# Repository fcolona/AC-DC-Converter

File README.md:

# Fonte de Tensão Variável

## Integrantes do Grupo
- Felipe Ferreira Colona - 15636525
- Arthur Martins Pereira - 16855601
- Gabriel Cordeiro Correa Silva - 16866642

## Descrição
O projeto se trata de uma fonte de tensão variável que, ao receber uma corrente alternada (AC), fornece uma corrente direta aproximadamente contínua (DC). Nesse contexto, deve ser possível regular a tensão de saída por meio de um potenciômetro, podendo escolher entre 3V e 12V e mantendo uma corrente de cerca de 100mA. Desse modo, a fonte deve ser capaz de carregar um celular sem causar danos.

## Componentes

| Quantidade      | Componente              | Valor    |
| --------------- | ----------------------- | -------  |
| 1x              | Ponte de diodos         | R$ 3,90  |
| 1x              | Capacitor               | R$ 4,40  |
| 1x              | Potenciômetro           | R$ 7,00  |
| 1x              | Diodo Zenner            | R$ 0,50  |
| 1x              | Transistor 2N2222       | R$ 2,55  |
| 5x              | Resistores 1/4W         | R$ 0,07  |
| 1x              | Resistor 2W             | R$ 1,20  |
| 1x              | LED                     | R$ 0,50  |
| 1x              | Jumper                  | R$ 0,70  |
| 1x              | Protoboard              | R$ 21,70 |
| TOTAL           |                         | R$ 42,80 |

#### Transformador
O transformador é responsável por diminuir o pico da tensão recebida da tomada de 180V para 18,1V. Essa transformação ocorre por meio da variação do campo magnético nas espiras do componente que causa uma indução de corrente elétrica.

#### Ponte de Diodo
A ponte de diodo é responsável por garantir que a corrente flua em somente um sentido ao longo do circuito. Isso é necessário, pois a tensão de entrada é uma senoide e, desse modo, possui uma parte negativa. Sendo assim, a ponte é composta por 4 diodos que, da forma em que estão dispostos, permitem a passagem de corrente em apenas um sentido.

#### Capacitor
O capacitor é responsável por continuar a fornecer tensão ao circuito mesmo nos mementos em que a senoide da tensão está com uma taxa de variação negativa, isto é, está diminuindo. Nesse sentido, o componente armazena carga quando a tensão está alta e libera carga quando a tensão de fora está menor do que a tensão do capacitor.

#### Resistor
O resistor é responsável por diminuir a corrente elétrica que chega a um outro componente. Isso é feito a fim de não ultrapassar a potência de operação do componente em questão e mantê-lo funcionando.

#### LED
O LED é responsável por facilitar a visualização do comportamento do circuito. Nesse sentido, o intuito é que ele se mantenha aceso durante todo o período. Assim, indicando que a corrente está de fato contínua (aproximadamente).

#### Diodo Zenner
O diodo zenner é reponsável por limitar a tensão máxima. No circuito em questão, ele limita a tensão em 13V que, após passar passar pelo transistor, se torna 12,3V.

#### Transistor
O transistor é responsável por amplificar o sinal que chega nele, de modo a fornecer 100 mA de corrente ao final do circuito.

#### Potenciômetro
O potenciômetro é responsável por possibilitar regular a tensão de saída (entre 3V e 12V).

## Circuito

[Link para o circuito](https://www.falstad.com/circuit/circuitjs.html?ctz=CQAgjCAMB0l3BWcMBMcUHYMGZIA4UA2ATmIxAUgpABZsKBTAWjDACgAnEQlG27FN1608VKmDhsA5iAFUefOdwSEoUThRp8EGVQi1C+VGhkkB3TdrCD9fGsVWQ2F+6teXaD9S68L+gvydsPgAvADcAewAbABcAQykGAB0ARzB6cWgMMDoEFDwwYnz8PDxsZnIqQXT1EM9VP3d3QXDo+MTU9OdDf3repy4mgT73cXhuhCK+yZsDJxdhukEhwXmKKdsKQipNpzAMbQMEaw8dVQgJeChoUkp4e-uIACUGAGcAS1f4gDsAYwYJgZGr5hGtCKUeptAt0-McAhC4eoYutliC7F5xCAWBhoPo8LoaAhcIRCMETjBCLpKXhiJB9qIDthyJcQAATBgAMziAFdYt0mF4lljCHZhmsWPleixtv02K8sdY8FLBWK1Fyoq8AQtlsMlEK1kK-EpoYNFiqAqDZOMwDxekL7V5BOyubyYkwogxWeA1GJYOwLMbhChhNCLMHRYI9WK2L9ZGheoG7Nd4CYQChsNBsDb0lpeKxCcFk3T1FxwUrEWWeuI0PybfJhEwRVW2GEFTKhdL60ZvTKwKIfdcEGwACrCiNxqu0a7pUqzudz4hYmCQGgoImQbaUyh9umLpgIG4YPAISjEfGbmjg5g5a6kYjdQVeM2Obp1lHgGUqMSv9vDN80OB1C9N8vzTYRmnAAA5ACVzYYDPxlR9VGqaC4BoOCwPRc5f0EFCYPQr0kI-YxhjwtCfx2KY31DYienDZsw3Ax0QxUbxMOUVRhkIVi1i41iuNBbpFl1VEXwsf9APomC2KkyTwOjCJ+G4bsANIWhMkcNMlOwNhFPjJtjEgNSAOuaotPjHTFIaFSjMXeNl2sJBcO4WQ2CAA)

## Design de PCB

## Imagem e Vídeo

## Cálculos

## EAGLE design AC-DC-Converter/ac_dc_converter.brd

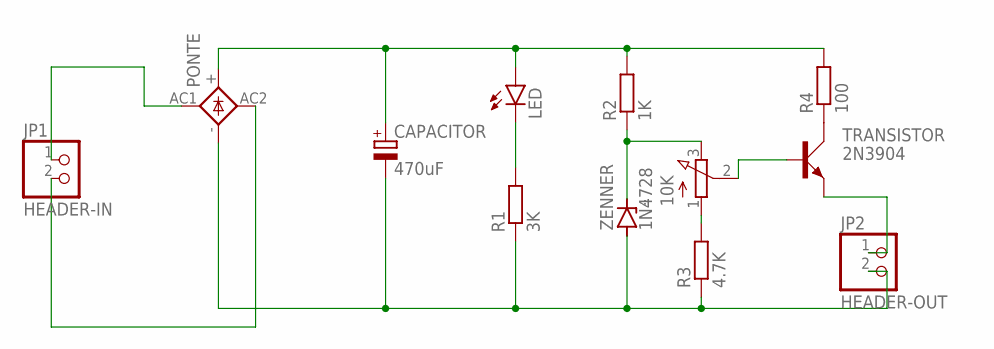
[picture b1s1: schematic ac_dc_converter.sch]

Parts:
CAPACITOR: 470uF; E5-10,5
JP1: HEADER-IN; 1X02
JP2: HEADER-OUT; 1X02
LED: LED5MM
PONTE: 1KAB
R1: 3K; 0204/7
R2: 1K; 0204/7
R3: 4.7K; 0204/7
R4: 100; 0204/7
TRANSISTOR: 2N3904; TO92D
ZENNER: 1N4728; DO41Z10
¨: 10K; 3RP/1610N

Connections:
unnamed: JP1.1, PONTE.AC1
unnamed: CAPACITOR.+, LED.A, PONTE.+, R2.2, R4.2
unnamed: R2.1, ZENNER.C, ¨.3 (E)
unnamed: CAPACITOR.-, JP2.2, PONTE.-, R1.1, R3.1, ZENNER.A
unnamed: JP1.2, PONTE.AC2
unnamed: LED.K (C), R1.2
unnamed: TRANSISTOR.B, ¨.2 (S)
unnamed: R4.1, TRANSISTOR.C
unnamed: JP2.1, TRANSISTOR.E
unnamed: R3.2, ¨.1 (A)

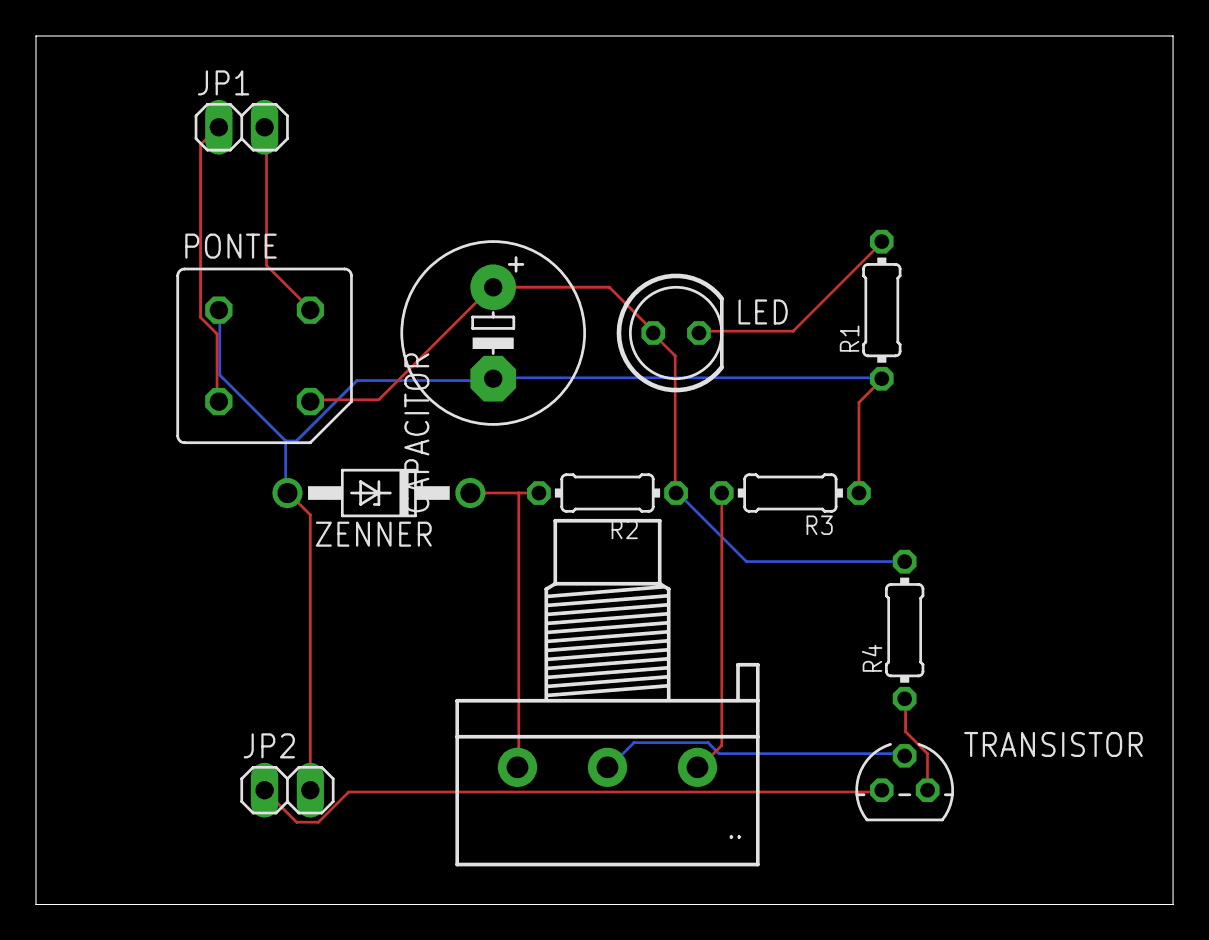
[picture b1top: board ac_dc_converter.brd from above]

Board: 2 copper layers, 63.2 x 48.2 mm, 12 parts (0 on the bottom side), 10 nets.

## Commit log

2025-06-02 add description and components explanations
2025-06-13 add circuit in Falstad and add calculations
2025-06-21 add schematic and PCB design done using Eagle
2025-06-21 alter circuit image
2025-06-29 add group members
2025-06-30 Tabela de preços
2025-07-04 add circuit image and video
